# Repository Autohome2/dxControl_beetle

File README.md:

# **DxControl CanBus Beetle**

# ** COMING SOON **

## About
This repo is for the Canbus interface for [Speeduino Ecu](https://github.com/noisymime/speeduino) using the _mega2560 boards_.

As they have no onboard Canbus interface this plugin "Beetle" offers the expansion.

### The PCB		
The PCB designed for the firmware uses a SAMD21 mcu directly onboard.
	
 - It has a MCP2515 Can interface chip and the External Can connections have esd protection.
	
 - There is space for a SPI EEPROM which can be enabled in the firmware rather than using the emulated eeprom.
	
 - There is a header for a SPI OLED display (128x32 or 128x64 currently) for simple display of realtime data.

 - There is also has a few spare io brought out to headers. 
   
   These can be configured in the firmware as Analog inputs, digital inputs and digital outputs(including pwm),dependant on firmware version.
   
### Use   
This module is configured via Tunerstudio and there is a ini file for that in the reference folder of each release version.
		
The module can be used standalone as a mini io controller or connected to the Speeduino Mega2560 serial3 port . 

Please see the Speeduino ECU  documentation regards enabling this port and configuring the modules use with it.
				
## V1.001
    Release Date : TBA
	This version offers.
	Basic Periodic broadcast of the Speeduino ECU Realtime data and any from configured module io pins
				
## V1.002
    Release Date : TBA
	
## The Future.............
	Future versions will offer
		The ability to source data from external can sources
		Output io and canbus signal based on logical operations on realtime and local data values
		offer a OBD2 style diagnostic port that can be read using a STD OBD reader or reader app eg Torque.
				
# Build the Beetle.
 The Beetle components are mainly surface mount(SMD), with a few through hole items(such as the headers).
 
 The SMD components are no smaller than 0805 size to enable hand construction.
 
 There are components on both sides of the pcb. It is best to leave the headers until last to solder in place.

 There are so many variations on build method for SMT that i will only suggest you choose the best suited to your capability and the equipment you have.

 That said it is possible to completely hand solder this board using a fine tipped iron!

 **Or if you dont feel able to build the board checkout one of the Speeduino distributors for stock of assembled or partially assembled devices.**

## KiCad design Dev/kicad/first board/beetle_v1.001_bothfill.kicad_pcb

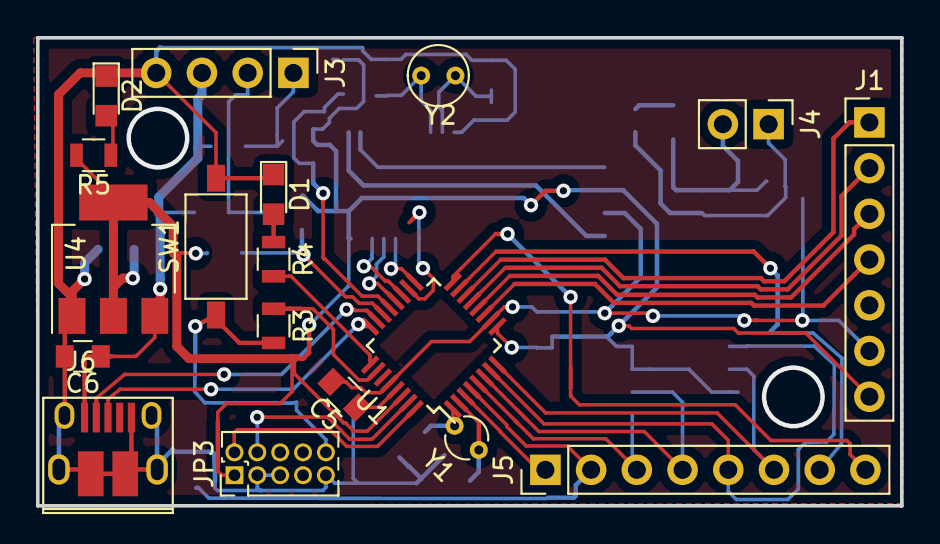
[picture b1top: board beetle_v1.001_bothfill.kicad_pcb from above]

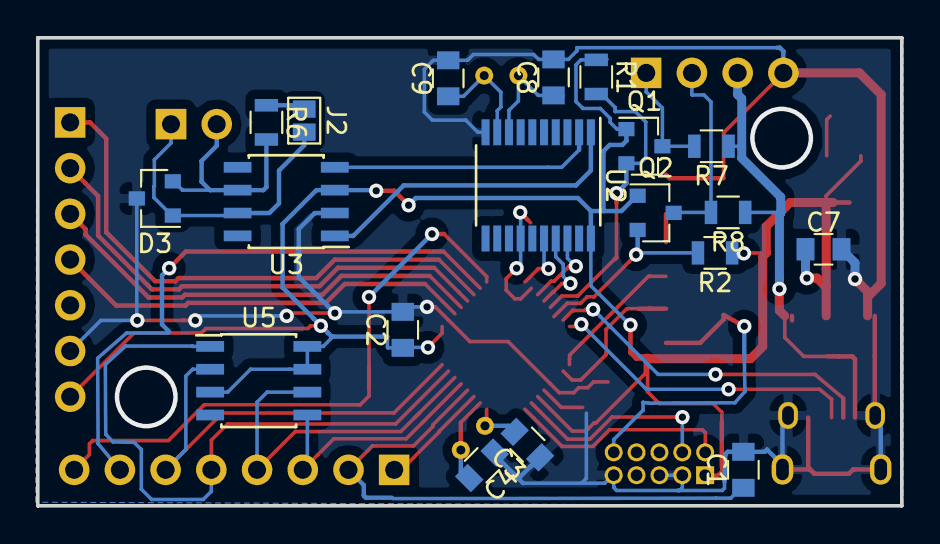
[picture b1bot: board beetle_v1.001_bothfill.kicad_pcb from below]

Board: 2 copper layers, 48.0 x 26.0 mm, 37 parts (19 on the bottom side), 42 nets.

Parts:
C1, C2: 100nF; C_0805
C3, C4: 22pF; C_0805
C5, C6, C7: 1uF; C_0805
C8, C9: 18pf; C_0805
D1: status_LED; LED_0805
D2: pwr_LED; LED_0805
D3: esdcan01; SOT-23
J1: spi disp; Pin_Header_Straight_1x07_Pitch2.54mm
J2: GS2
J3: ECU; Pin_Header_Straight_1x04_Pitch2.54mm
J4: CAN; Pin_Header_Straight_1x02_Pitch2.54mm
J5: Aux io; Pin_Header_Straight_1x08_Pitch2.54mm
J6: USB_B_Micro; USB_Micro-B_10103594-0001LF_daz
JP3: CONNETTORI_0171_PH127-205DF055G00A; Pin_Header_Straight_2x05_Pitch1.27mm
Q1, Q2: 2N7002; SOT-23
R1, R2, R7, R8: 10k; R_0805
R3, R4, R5: 330; R_0805
R6: 120R; R_0805
SW1: SW_Push; SW_SPST_3x6x2.5
U1: ATSAMD21E18A-MU; LQFP-32_5x5mm_Pitch0.5mm
U2: MCP2515-EST; TSSOP-20_4.4x6.5mm_Pitch0.65mm
U3: MCP2562-E-SN; SOIC-8_3.9x4.9mm_Pitch1.27mm
U4: LM1117-3.3; SOT-223-3_TabPin2
U5: AT25128 SPI EEPROM; SOIC-8_3.9x4.9mm_Pitch1.27mm
Y1: ABS07-32.768KHZ; Crystal_Round_d2.0mm_Vertical
Y2: 16MHZ; Crystal_Round_d3.0mm_Vertical

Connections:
3.3V: C2.1, C7.1, J1.7, JP3.1, Q1.1, Q2.1, R1.1, R2.1, R5.2, U1.9, U1.30, U2.20, U3.3, U4.2, U5.3, U5.7, U5.8
5V: C6.1, J3.3, J6.1, R7.1, R8.1, U4.3
/1mcu/MISO-DISP: J1.1, U1.14
/1mcu/MOSI-DISP: J1.4, U1.11
/1mcu/PA02_AIN0: J5.1, U1.3
/1mcu/PA03_AIN1: C1.1, J5.2, U1.4
/1mcu/PA04_GPIO1_MOSI_EEPROM: J5.3, U1.5, U5.5
/1mcu/PA05_GPIO2_SCK_EEPROM: J5.4, U1.6, U5.6
/1mcu/PA06_GPIO3_SS_EEPROM: J5.5, U1.7, U5.1
/1mcu/PA07_GPIO4_MISO_EEPROM: J5.6, U1.8, U5.2
/1mcu/PA14_TCC0-W4: J5.7, U1.15
/1mcu/PA15_TCC0-W5: J5.8, U1.16
/1mcu/PA22_5V_RX0: J3.1, Q1.3, R7.2
/1mcu/PA22_RX0: Q1.2, R1.2, U1.21
/1mcu/PA23_5V_TX0: J3.2, Q2.3, R8.2
/1mcu/PA23_TX0: Q2.2, R2.2, U1.22
/1mcu/PA27_TX_LED: R4.2, U1.25
/1mcu/PA30_SWCLK: JP3.4, U1.31
/1mcu/PA31_SWDIO: JP3.2, U1.32
/1mcu/RESET: JP3.10, R3.2, SW1.1
/1mcu/SCK-DISP: J1.3, U1.12
/1mcu/SS-DISP: J1.2, U1.13
/1mcu/TARGET_RESET_EDBG: R3.1, U1.26
CAN1H: D3.1, J2.2, J4.1, U3.7
CAN1L: D3.2, J4.2, R6.2, U3.6
GND: C1.2, C2.2, C3.1, C4.1, C5.2, C6.2, C7.2, C8.2, C9.2, D1.1, D2.1, D3.3, J1.6, J3.4, J6.5, J6.6, JP3.3, JP3.5, JP3.9, SW1.2, U1.10, U1.28, U2.10, U3.2, U4.1
MISO: U1.20, U2.17
MOSI: U1.17, U2.16
unnamed: C3.2, U1.1, Y1.2
unnamed: C4.2, U1.2, Y1.1
unnamed: C5.1, U1.29
unnamed: C8.1, U2.8, Y2.1
unnamed: C9.1, U2.9, Y2.2
unnamed: D1.2, R4.1
unnamed: D2.2, R5.1
unnamed: J2.1, R6.1
unnamed: U2.1, U3.1
unnamed: U2.2, U3.4
SCK: U1.18, U2.14
SS: U1.19, U2.18
TARGET_USB_N: J6.2, U1.23
TARGET_USB_P: J6.3, U1.24

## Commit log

2019-01-11 update readme and file structure
2019-01-11 changes to readme
2019-01-11 readme changes
